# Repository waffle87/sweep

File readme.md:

# Sweep

A [Ferris Sweep](https://github.com/davidphilipbarr/Sweep) variant designed with an integrated RP2040 and some other added features.

## Comments & Modifications
This PCB has the exact same dimensions and mounting points (via SplitKB Tenting Puck mount) as original Sweep PCB, making it compatible with most existing cases. Due to the use of USB-C interconnects opposed to TRRS jacks, this PCB is **not** compatible with "high-profile" cases or cases that have a cutout for TRRS jacks. This PCB only supports soldered Choc V1 switches, as it is common to build this keyboard without a plate. Some other modifications include:
- Per-key RGB lighting and underglow
- Support for a 135x240 ST7789 LCD via an FPC connector/cable
- USB-C interconnects with full-duplex serial communication
- VBUS detection for setting handedness
- Current and voltage reading sensor
- RGB data level-shifted to 5v

## Ordering
The following instructions will be for [JLCPCB](https://jlcpcb.com), but should generally apply to most PCB manufacturers. If you would like a plate, the one [here](https://github.com/davidphilipbarr/Sweep/blob/main/Sweep%20v2.2/sweepv2_plate.pro) can probably be used, although I have not verified this.

1. Upload the Gerber files from [production/gerbers.zip](production/gerbers.zip)
2. Set the following parameters: (and change other things like PCB quantity and colour as desired)
- **Different Design**: 2
3. For PCB assembly, choose **Economic** PCBA type and **Top Side** for assembly side. If you would like the LEDs and related components to be installed by PCBA, choose **Standard** and **Both Sides**.
4. Upload the [BOM](production/bom.csv) and [CPL](production/positions.csv) files
5. Ensure the correct components have been selected, and all are in stock. An effort has been made to choose as few extended components as possible, but this is not possible for some.
- Footprints D1 & D2 are power indication LEDs. They can be left unpopulated if you'd rather not have an LED that is always lit. If you would like them installed while not being blinded, try to find an LED with a lower forward current and voltage (supply is 5v), perhaps something in the realm of 2v and 1-5mA.
- The current-smoothing capacitors (on the back side) for the RGB LEDs are not required for the LEDs to function.
- The FPC connector is only needed if you'd wish to install the ST7789 display(s).
6. Give a quick look at the component placement and make sure nothing looks wildly wrong. It is normal for some components to be shown oriented incorrectly or not quite where they belong. The PCB reviewers will usually correct this without issue.

### Additional components
For optional components to be installed by hand:
| Item | Quantity | Remarks |
|------|----------|---------|
| ST7789 135x240 Display ([Aliexpress](https://www.aliexpress.us/item/3256803585877182.html)) | 2 | Others with a matching pinout and 0.5mm pitch should work |
| Acrylic Cover ([cover.dxf](cover.dxf)) | 2 | Each uses 4x ~4mm M2 screws and 2x ~4mm M2 standofffs |

## Build Instructions
These steps assume you already have an assembled PCB and are installing switches, RGB LEDs, and/or displays. If you are hand-assembling the PCBs with all components, the [interactive BOM](https://html-preview.github.io/?url=https://github.com/waffle87/sweep/blob/master/ibom.html) will be helpful.

1. Ensure keyboard is functional by flashing firmware and testing by shorting switch footprint pins with metal tweezers. This should output keypresses on the computer.
2. Install RGB LEDs if desired. The chopped-off corner should align with the marked corner on PCB - this applies to both per-key and underglow LEDs. Please double check orientation, as an incorrectly oriented LED will result in keyboard not working. It is wise to test the LEDs as you install them (eg. install a couple, then plug in keyboard). The per-key LEDs will need to be installed and working before the underglow LEDs will work.
- If you choose to install the capacitors, do so at this step as well. They do not have a specific orientation.
3. Install displays if desired. Open FPC connector, insert display cable with contacts facing upward, close connector. The displays can be secured by some double sided tape, or carefully applying some hot glue.
4. Install switches, keycaps, case, and enjoy your keyboard!

## Firmware
QMK Firmware support for this keyboard can be found [here](https://git.pngu.org/qmk_me/tree/keyboards/sweep). Enter bootloader mode by holding BOOT button and tapping RESET button. If your PCBs are revision 0.1.0 (or have commit `2fa9763` labeled on them), you should use the code from [this commit](https://git.pngu.org/qmk_me/tree/keyboards/sweep?id=b0c6852154b3060b639e8d7d87d16d17bd4dfcc4) or prior.

## Changelog
### 0.2.0
- Remove Cirque trackpad support
- Remove nice!view and I2C OLED support
- Update to Kicad 9.0.2
- Add ST7789 LCD support
- Update acrylic cover and its mounting points
- Add voltage sensor support

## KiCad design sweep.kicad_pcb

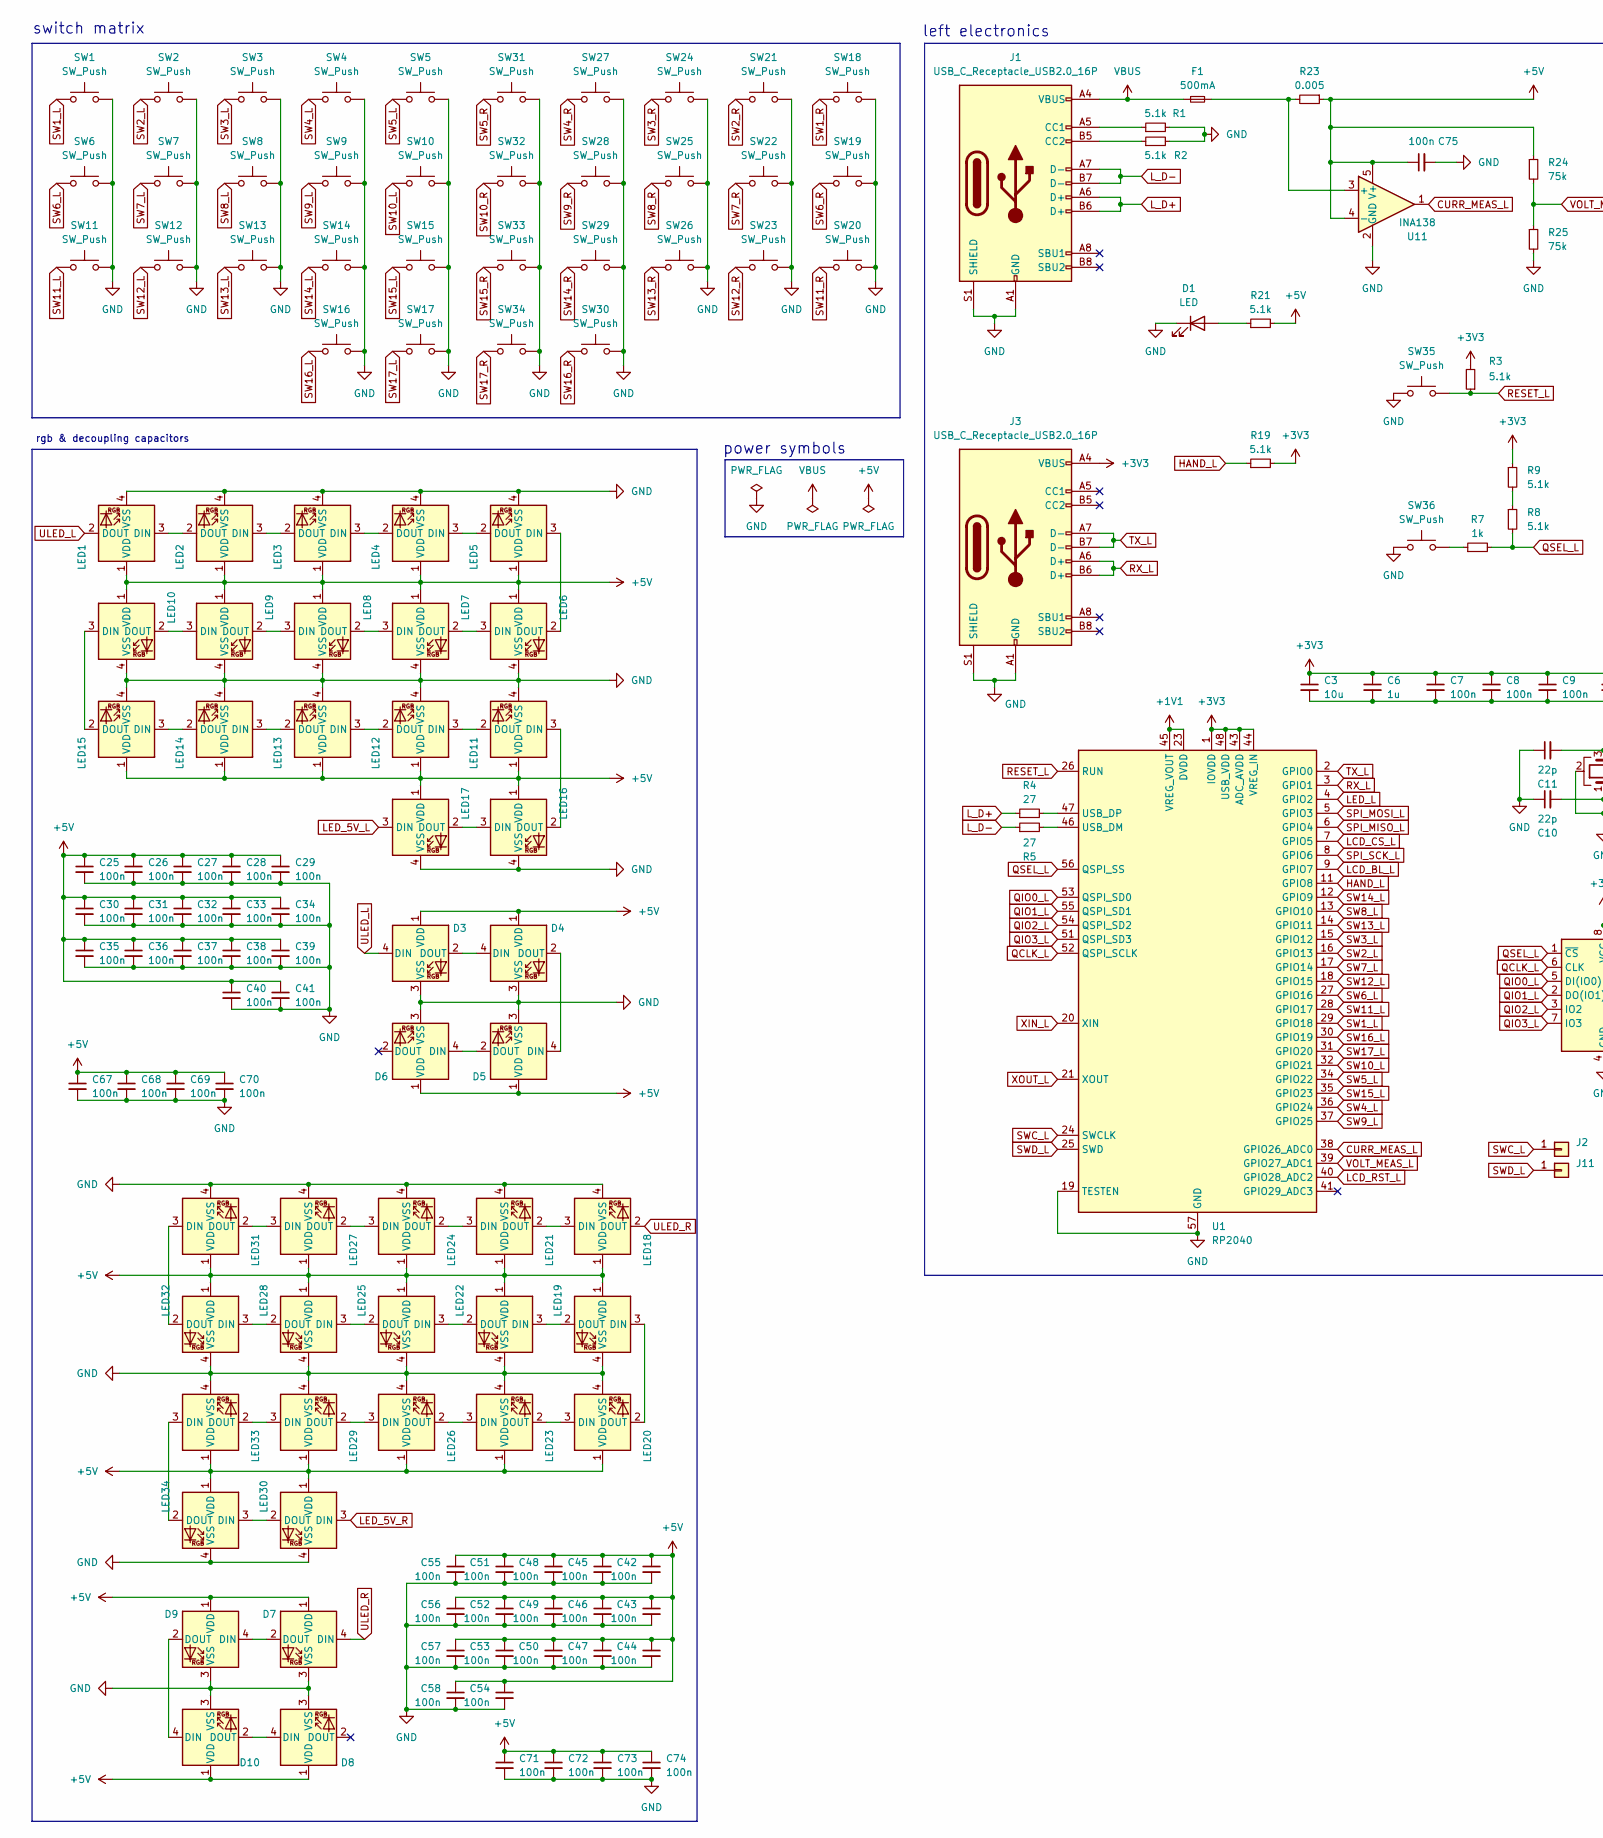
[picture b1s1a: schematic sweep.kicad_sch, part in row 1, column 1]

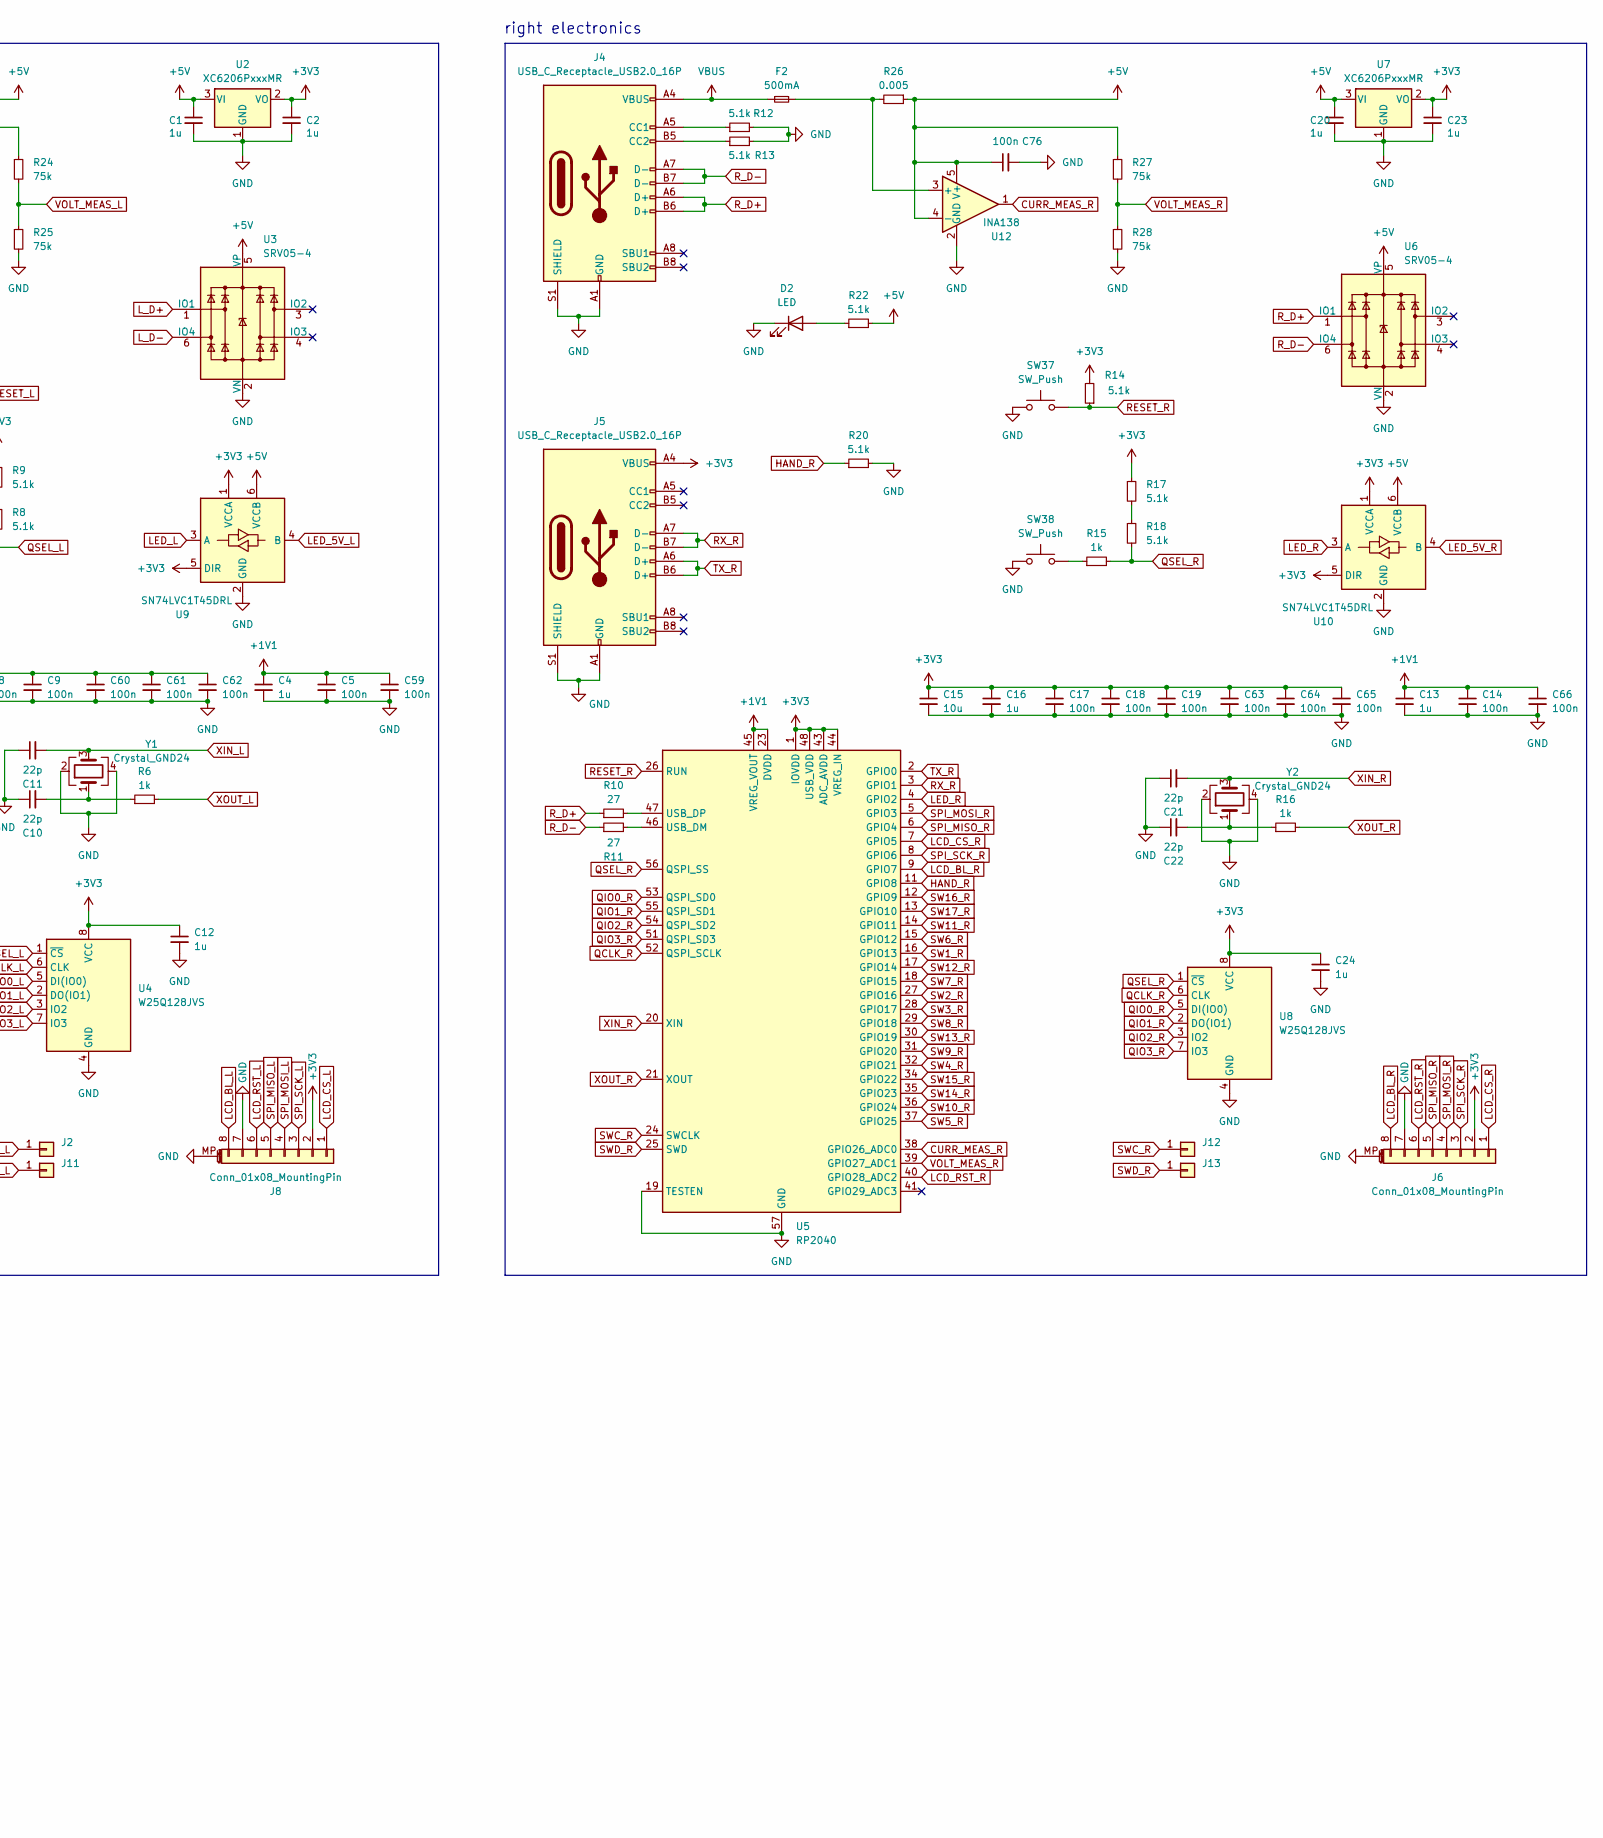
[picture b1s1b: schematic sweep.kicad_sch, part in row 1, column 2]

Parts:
C1, C2, C4, C6, C12, C13, C16, C20, C23, C24: 1u; C_0402_1005Metric
C3, C15: 10u; C_0603_1608Metric
C5, C7, C8, C9, C14, C17, C18, C19, C25, C26, C27, C28, C29, C30, C31, C32, C33, C34, C35, C36, C37, C38, C39, C40, C41, C42, C43, C44, C45, C46, C47, C48, C49, C50, C51, C52, C53, C54, C55, C56, C57, C58, C59, C60, C61, C62, C63, C64, C65, C66, C67, C68, C69, C70, C71, C72, C73, C74, C75, C76: 100n; C_0402_1005Metric
C10, C11, C21, C22: 22p; C_0402_1005Metric
D1, D2: LED; LED_0603_1608Metric
D3, D4, D5, D6, D7, D8, D9, D10: WS2812B; LED_WS2812B-Mini_PLCC4_3.5x3.5mm
F1, F2: 500mA; Fuse_1206_3216Metric
J1, J3, J4, J5: USB_C_Receptacle_USB2.0_16P; USB_C_Receptacle_HRO_TYPE-C-31-M-12
J2, J11, J12, J13: Conn_01x01; TestPoint_Pad_D1.0mm
J6, J8: Conn_01x08_MountingPin; TE_0-1734839-8_1x08-1MP_P0.5mm_Horizontal
LED1, LED2, LED3, LED4, LED5, LED6, LED7, LED8, LED9, LED10, LED11, LED12, LED13, LED14, LED15, LED16, LED17, LED18, LED19, LED20, LED21, LED22, LED23, LED24, LED25, LED26, LED27, LED28, LED29, LED30, LED31, LED32, LED33, LED34: choc_SK6812MINI-E; LED_choc_6028R
R1, R2, R3, R8, R9, R12, R13, R14, R17, R18, R19, R20, R21, R22: 5.1k; R_0402_1005Metric
R4, R5, R10, R11: 27; R_0402_1005Metric
R6, R7, R15, R16: 1k; R_0402_1005Metric
R23, R26: 0.005; R_1206_3216Metric
R24, R25, R27, R28: 75k; R_0402_1005Metric
SW1, SW2, SW3, SW4, SW5, SW6, SW7, SW8, SW9, SW10, SW11, SW12, SW13, SW14, SW15, SW16, SW17, SW18, SW19, SW20, SW21, SW22, SW23, SW24, SW25, SW26, SW27, SW28, SW29, SW30, SW31, SW32, SW33, SW34: SW_Push; SW_choc_v1_1u
SW35, SW36, SW37, SW38: SW_Push; SW_SPST_B3U-1000P
U1, U5: RP2040; QFN-56-1EP_7x7mm_P0.4mm_EP3.2x3.2mm
U2, U7: XC6206PxxxMR; SOT-23-3
U3, U6: SRV05-4; SOT-23-6-routable
U4, U8: W25Q128JVS; SOIC-8_5.23x5.23mm_P1.27mm
U9, U10: SN74LVC1T45DRL; SOT-563
U11, U12: INA138; SOT-23-5
Y1, Y2: Crystal_GND24; Crystal_SMD_3225-4Pin_3.2x2.5mm

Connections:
+1V1: C4.1, C5.1, C13.1, C14.1, C59.1, C66.1, U1.23 (DVDD), U1.45 (VREG_VOUT), U1.50 (DVDD), U5.23 (DVDD), U5.45 (VREG_VOUT), U5.50 (DVDD)
+3V3: C2.1, C3.1, C6.1, C7.1, C8.1, C9.1, C12.1, C15.1, C16.1, C17.1, C18.1, C19.1, C23.1, C24.1, C60.1, C61.1, C62.1, C63.1, C64.1, C65.1, J3.A4 (VBUS), J3.A9 (VBUS), J3.B4 (VBUS), J3.B9 (VBUS), J5.A4 (VBUS), J5.A9 (VBUS), J5.B4 (VBUS), J5.B9 (VBUS), J6.2, J8.2, R3.2, R9.1, R14.2, R17.1, R19.2, U1.1 (IOVDD), U1.10 (IOVDD), U1.22 (IOVDD), U1.33 (IOVDD), U1.42 (IOVDD), U1.43 (ADC_AVDD), U1.44 (VREG_IN), U1.48 (USB_VDD), U1.49 (IOVDD), U2.2 (VO), U4.8 (VCC), U5.1 (IOVDD), U5.10 (IOVDD), U5.22 (IOVDD), U5.33 (IOVDD), U5.42 (IOVDD), U5.43 (ADC_AVDD), U5.44 (VREG_IN), U5.48 (USB_VDD), U5.49 (IOVDD), U7.2 (VO), U8.8 (VCC), U9.1 (VCCA), U9.5 (DIR), U10.1 (VCCA), U10.5 (DIR)
+5V: C1.1, C20.1, C25.1, C26.1, C27.1, C28.1, C29.1, C30.1, C31.1, C32.1, C33.1, C34.1, C35.1, C36.1, C37.1, C38.1, C39.1, C40.1, C41.1, C42.1, C43.1, C44.1, C45.1, C46.1, C47.1, C48.1, C49.1, C50.1, C51.1, C52.1, C53.1, C54.1, C55.1, C56.1, C57.1, C58.1, C67.1, C68.1, C69.1, C70.1, C71.1, C72.1, C73.1, C74.1, C75.1, C76.1, D3.1 (VDD), D4.1 (VDD), D5.1 (VDD), D6.1 (VDD), D7.1 (VDD), D8.1 (VDD), D9.1 (VDD), D10.1 (VDD), LED1.1 (VDD), LED2.1 (VDD), LED3.1 (VDD), LED4.1 (VDD), LED5.1 (VDD), LED6.1 (VDD), LED7.1 (VDD), LED8.1 (VDD), LED9.1 (VDD), LED10.1 (VDD), LED11.1 (VDD), LED12.1 (VDD), LED13.1 (VDD), LED14.1 (VDD), LED15.1 (VDD), LED16.1 (VDD), LED17.1 (VDD), LED18.1 (VDD), LED19.1 (VDD), LED20.1 (VDD), LED21.1 (VDD), LED22.1 (VDD), LED23.1 (VDD), LED24.1 (VDD), LED25.1 (VDD), LED26.1 (VDD), LED27.1 (VDD), LED28.1 (VDD), LED29.1 (VDD), LED30.1 (VDD), LED31.1 (VDD), LED32.1 (VDD), LED33.1 (VDD), LED34.1 (VDD), R21.2, R22.2, R23.1, R24.1, R26.1, R27.1, U2.3 (VI), U3.5 (VP), U6.5 (VP), U7.3 (VI), U9.6 (VCCB), U10.6 (VCCB), U11.4 (-), U11.5 (V+), U12.4 (-), U12.5 (V+)
CURR_MEAS_L: U1.38 (GPIO26_ADC0), U11.1
CURR_MEAS_R: U5.38 (GPIO26_ADC0), U12.1
GND: C1.2, C2.2, C3.2, C4.2, C5.2, C6.2, C7.2, C8.2, C9.2, C10.1, C11.1, C12.2, C13.2, C14.2, C15.2, C16.2, C17.2, C18.2, C19.2, C20.2, C21.1, C22.1, C23.2, C24.2, C25.2, C26.2, C27.2, C28.2, C29.2, C30.2, C31.2, C32.2, C33.2, C34.2, C35.2, C36.2, C37.2, C38.2, C39.2, C40.2, C41.2, C42.2, C43.2, C44.2, C45.2, C46.2, C47.2, C48.2, C49.2, C50.2, C51.2, C52.2, C53.2, C54.2, C55.2, C56.2, C57.2, C58.2, C59.2, C60.2, C61.2, C62.2, C63.2, C64.2, C65.2, C66.2, C67.2, C68.2, C69.2, C70.2, C71.2, C72.2, C73.2, C74.2, C75.2, C76.2, D1.1 (K), D2.1 (K), D3.3 (VSS), D4.3 (VSS), D5.3 (VSS), D6.3 (VSS), D7.3 (VSS), D8.3 (VSS), D9.3 (VSS), D10.3 (VSS), J1.A1 (GND), J1.A12 (GND), J1.B1 (GND), J1.B12 (GND), J1.S1 (SHIELD), J3.A1 (GND), J3.A12 (GND), J3.B1 (GND), J3.B12 (GND), J3.S1 (SHIELD), J4.A1 (GND), J4.A12 (GND), J4.B1 (GND), J4.B12 (GND), J4.S1 (SHIELD), J5.A1 (GND), J5.A12 (GND), J5.B1 (GND), J5.B12 (GND), J5.S1 (SHIELD), J6.7, J6.MP (MountPin), J8.7, J8.MP (MountPin), LED1.4 (VSS), LED2.4 (VSS), LED3.4 (VSS), LED4.4 (VSS), LED5.4 (VSS), LED6.4 (VSS), LED7.4 (VSS), LED8.4 (VSS), LED9.4 (VSS), LED10.4 (VSS), LED11.4 (VSS), LED12.4 (VSS), LED13.4 (VSS), LED14.4 (VSS), LED15.4 (VSS), LED16.4 (VSS), LED17.4 (VSS), LED18.4 (VSS), LED19.4 (VSS), LED20.4 (VSS), LED21.4 (VSS), LED22.4 (VSS), LED23.4 (VSS), LED24.4 (VSS), LED25.4 (VSS), LED26.4 (VSS), LED27.4 (VSS), LED28.4 (VSS), LED29.4 (VSS), LED30.4 (VSS), LED31.4 (VSS), LED32.4 (VSS), LED33.4 (VSS), LED34.4 (VSS), R1.2, R2.2, R12.2, R13.2, R20.2, R25.2, R28.2, SW1.2, SW2.2, SW3.2, SW4.2, SW5.2, SW6.2, SW7.2, SW8.2, SW9.2, SW10.2, SW11.2, SW12.2, SW13.2, SW14.2, SW15.2, SW16.2, SW17.2, SW18.1, SW19.1, SW20.1, SW21.1, SW22.1, SW23.1, SW24.1, SW25.1, SW26.1, SW27.1, SW28.1, SW29.1, SW30.1, SW31.1, SW32.1, SW33.1, SW34.1, SW35.1, SW36.1, SW37.1, SW38.1, U1.19 (TESTEN), U1.57 (GND), U2.1 (GND), U3.2 (VN), U4.4 (GND), U5.19 (TESTEN), U5.57 (GND), U6.2 (VN), U7.1 (GND), U8.4 (GND), U9.2 (GND), U10.2 (GND), U11.2 (GND), U12.2 (GND), Y1.2, Y1.4, Y2.2, Y2.4
HAND_L: R19.1, U1.11 (GPIO8)
HAND_R: R20.1, U5.11 (GPIO8)
LCD_BL_L: J8.8, U1.9 (GPIO7)
LCD_BL_R: J6.8, U5.9 (GPIO7)
LCD_CS_L: J8.1, U1.7 (GPIO5)
LCD_CS_R: J6.1, U5.7 (GPIO5)
LCD_RST_L: J8.6, U1.40 (GPIO28_ADC2)
LCD_RST_R: J6.6, U5.40 (GPIO28_ADC2)
LED_5V_L: LED17.3 (DIN), U9.4 (B)
LED_5V_R: LED30.3 (DIN), U10.4 (B)
LED_L: U1.4 (GPIO2), U9.3 (A)
LED_R: U5.4 (GPIO2), U10.3 (A)
L_D+: J1.A6 (D+), J1.B6 (D+), R4.1, U3.1 (IO1)
L_D-: J1.A7 (D-), J1.B7 (D-), R5.1, U3.6 (IO4)
unnamed: C10.2, R6.1, Y1.1
unnamed: C22.2, R16.1, Y2.1
unnamed: D1.2 (A), R21.1
unnamed: D2.2 (A), R22.1
unnamed: D3.2 (DOUT), D4.4 (DIN)
unnamed: D4.2 (DOUT), D5.4 (DIN)
unnamed: D5.2 (DOUT), D6.4 (DIN)
unnamed: D7.2 (DOUT), D9.4 (DIN)
unnamed: D9.2 (DOUT), D10.4 (DIN)
unnamed: D8.4 (DIN), D10.2 (DOUT)
unnamed: J1.A5 (CC1), R1.1
unnamed: J1.B5 (CC2), R2.1
unnamed: J4.A5 (CC1), R12.1
unnamed: J4.B5 (CC2), R13.1
unnamed: LED1.3 (DIN), LED2.2 (DOUT)
unnamed: LED2.3 (DIN), LED3.2 (DOUT)
unnamed: LED3.3 (DIN), LED4.2 (DOUT)
unnamed: LED4.3 (DIN), LED5.2 (DOUT)
unnamed: LED5.3 (DIN), LED6.2 (DOUT)
unnamed: LED6.3 (DIN), LED7.2 (DOUT)
unnamed: LED7.3 (DIN), LED8.2 (DOUT)
unnamed: LED8.3 (DIN), LED9.2 (DOUT)
unnamed: LED10.3 (DIN), LED15.2 (DOUT)
unnamed: LED9.3 (DIN), LED10.2 (DOUT)
unnamed: LED11.3 (DIN), LED16.2 (DOUT)
unnamed: LED11.2 (DOUT), LED12.3 (DIN)
unnamed: LED12.2 (DOUT), LED13.3 (DIN)
unnamed: LED13.2 (DOUT), LED14.3 (DIN)
unnamed: LED14.2 (DOUT), LED15.3 (DIN)
unnamed: LED16.3 (DIN), LED17.2 (DOUT)
unnamed: LED18.3 (DIN), LED21.2 (DOUT)
unnamed: LED19.3 (DIN), LED20.2 (DOUT)
unnamed: LED19.2 (DOUT), LED22.3 (DIN)
unnamed: LED20.3 (DIN), LED23.2 (DOUT)
unnamed: LED21.3 (DIN), LED24.2 (DOUT)
unnamed: LED22.2 (DOUT), LED25.3 (DIN)
unnamed: LED23.3 (DIN), LED26.2 (DOUT)
unnamed: LED24.3 (DIN), LED27.2 (DOUT)
unnamed: LED25.2 (DOUT), LED28.3 (DIN)
unnamed: LED26.3 (DIN), LED29.2 (DOUT)
unnamed: LED27.3 (DIN), LED31.2 (DOUT)
unnamed: LED28.2 (DOUT), LED32.3 (DIN)
unnamed: LED29.3 (DIN), LED33.2 (DOUT)
unnamed: LED30.2 (DOUT), LED34.3 (DIN)
unnamed: LED31.3 (DIN), LED32.2 (DOUT)
unnamed: LED33.3 (DIN), LED34.2 (DOUT)
unnamed: R7.1, SW36.2
unnamed: R8.1, R9.2
unnamed: R15.1, SW38.2
unnamed: R17.2, R18.1
unnamed: R5.2, U1.46 (USB_DM)
unnamed: R4.2, U1.47 (USB_DP)
unnamed: R11.2, U5.46 (USB_DM)
unnamed: R10.2, U5.47 (USB_DP)
unnamed: F1.2, R23.2, U11.3 (+)
unnamed: F2.2, R26.2, U12.3 (+)
QCLK_L: U1.52 (QSPI_SCLK), U4.6 (CLK)
QCLK_R: U5.52 (QSPI_SCLK), U8.6 (CLK)
QIO0_L: U1.53 (QSPI_SD0), U4.5 (DI(IO0))
QIO0_R: U5.53 (QSPI_SD0), U8.5 (DI(IO0))
QIO1_L: U1.55 (QSPI_SD1), U4.2 (DO(IO1))
QIO1_R: U5.55 (QSPI_SD1), U8.2 (DO(IO1))
QIO2_L: U1.54 (QSPI_SD2), U4.3 (IO2)
QIO2_R: U5.54 (QSPI_SD2), U8.3 (IO2)
QIO3_L: U1.51 (QSPI_SD3), U4.7 (IO3)
QIO3_R: U5.51 (QSPI_SD3), U8.7 (IO3)
QSEL_L: R7.2, R8.2, U1.56 (QSPI_SS), U4.1 (~CS)
QSEL_R: R15.2, R18.2, U5.56 (QSPI_SS), U8.1 (~CS)
RESET_L: R3.1, SW35.2, U1.26 (RUN)
RESET_R: R14.1, SW37.2, U5.26 (RUN)
RX_L: J3.A6 (D+), J3.B6 (D+), U1.3 (GPIO1)
RX_R: J5.A7 (D-), J5.B7 (D-), U5.3 (GPIO1)
R_D+: J4.A6 (D+), J4.B6 (D+), R10.1, U6.1 (IO1)
R_D-: J4.A7 (D-), J4.B7 (D-), R11.1, U6.6 (IO4)
SPI_MISO_L: J8.5, U1.6 (GPIO4)
SPI_MISO_R: J6.5, U5.6 (GPIO4)
SPI_MOSI_L: J8.4, U1.5 (GPIO3)
SPI_MOSI_R: J6.4, U5.5 (GPIO3)
SPI_SCK_L: J8.3, U1.8 (GPIO6)
SPI_SCK_R: J6.3, U5.8 (GPIO6)
SW1_L: SW1.1, U1.29 (GPIO18)
SW1_R: SW18.2, U5.16 (GPIO13)
SW2_L: SW2.1, U1.16 (GPIO13)
SW2_R: SW21.2, U5.27 (GPIO16)
SW3_L: SW3.1, U1.15 (GPIO12)
SW3_R: SW24.2, U5.28 (GPIO17)
SW4_L: SW4.1, U1.36 (GPIO24)
SW4_R: SW27.2, U5.32 (GPIO21)
SW5_L: SW5.1, U1.34 (GPIO22)
SW5_R: SW31.2, U5.37 (GPIO25)
SW6_L: SW6.1, U1.27 (GPIO16)
SW6_R: SW19.2, U5.15 (GPIO12)
SW7_L: SW7.1, U1.17 (GPIO14)
SW7_R: SW22.2, U5.18 (GPIO15)
SW8_L: SW8.1, U1.13 (GPIO10)
SW8_R: SW25.2, U5.29 (GPIO18)
SW9_L: SW9.1, U1.37 (GPIO25)
SW9_R: SW28.2, U5.31 (GPIO20)
SW10_L: SW10.1, U1.32 (GPIO21)
SW10_R: SW32.2, U5.36 (GPIO24)
SW11_L: SW11.1, U1.28 (GPIO17)
SW11_R: SW20.2, U5.14 (GPIO11)
SW12_L: SW12.1, U1.18 (GPIO15)
SW12_R: SW23.2, U5.17 (GPIO14)
SW13_L: SW13.1, U1.14 (GPIO11)
SW13_R: SW26.2, U5.30 (GPIO19)
SW14_L: SW14.1, U1.12 (GPIO9)
SW14_R: SW29.2, U5.35 (GPIO23)
SW15_L: SW15.1, U1.35 (GPIO23)
SW15_R: SW33.2, U5.34 (GPIO22)
SW16_L: SW16.1, U1.30 (GPIO19)
SW16_R: SW30.2, U5.12 (GPIO9)
SW17_L: SW17.1, U1.31 (GPIO20)
SW17_R: SW34.2, U5.13 (GPIO10)
SWC_L: J2.1, U1.24 (SWCLK)
SWC_R: J12.1, U5.24 (SWCLK)
SWD_L: J11.1, U1.25 (SWD)
SWD_R: J13.1, U5.25 (SWD)
TX_L: J3.A7 (D-), J3.B7 (D-), U1.2 (GPIO0)
TX_R: J5.A6 (D+), J5.B6 (D+), U5.2 (GPIO0)
ULED_L: D3.4 (DIN), LED1.2 (DOUT)
ULED_R: D7.4 (DIN), LED18.2 (DOUT)
VBUS: F1.1, F2.1, J1.A4 (VBUS), J1.A9 (VBUS), J1.B4 (VBUS), J1.B9 (VBUS), J4.A4 (VBUS), J4.A9 (VBUS), J4.B4 (VBUS), J4.B9 (VBUS)
VOLT_MEAS_L: R24.2, R25.1, U1.39 (GPIO27_ADC1)
VOLT_MEAS_R: R27.2, R28.1, U5.39 (GPIO27_ADC1)
XIN_L: C11.2, U1.20 (XIN), Y1.3
XIN_R: C21.2, U5.20 (XIN), Y2.3
XOUT_L: R6.2, U1.21 (XOUT)
XOUT_R: R16.2, U5.21 (XOUT)

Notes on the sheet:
switch matrix
rgb & decoupling capacitors
left electronics
power symbols
right electronics

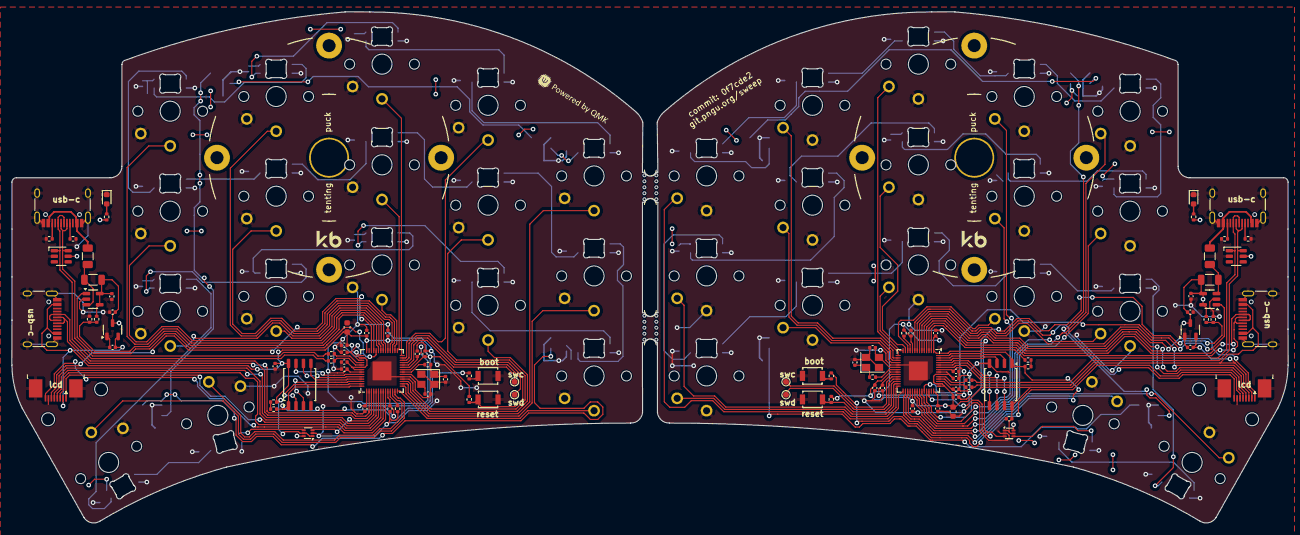
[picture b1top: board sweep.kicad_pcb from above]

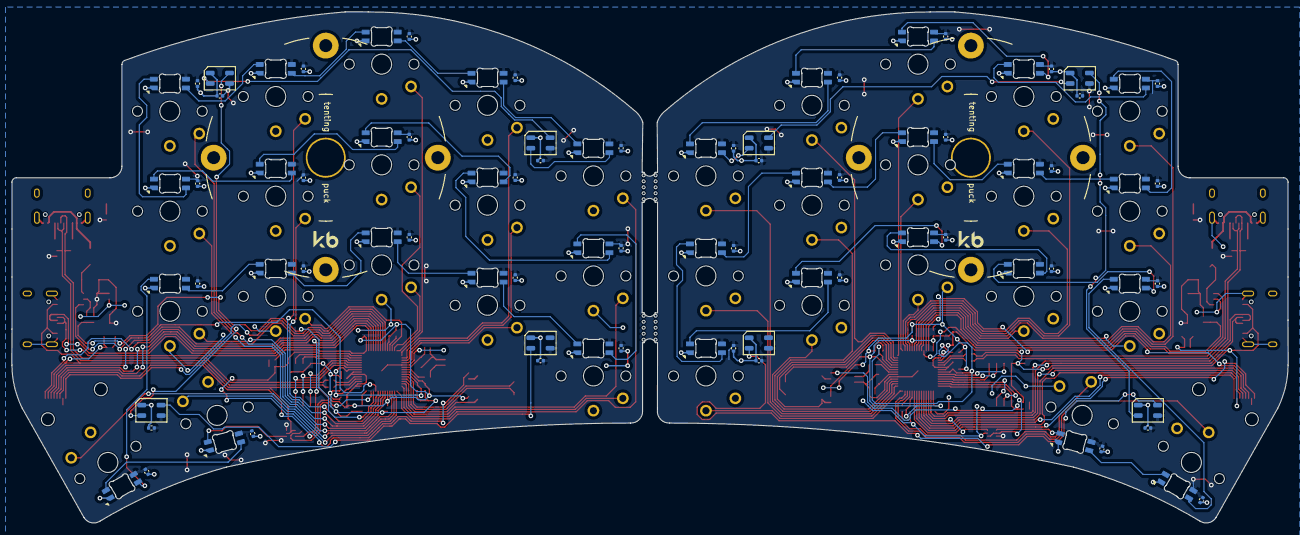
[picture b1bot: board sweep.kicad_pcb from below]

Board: 2 copper layers, 216.9 x 86.9 mm, 214 parts (84 on the bottom side), 149 nets.

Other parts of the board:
mouse-bite-2mm-slot, mouse-bite-2mm-slot#2: VAL**; mouse-bite-5mm-slot-with-space-for-track

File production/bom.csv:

Designator,Footprint,Quantity,Value,LCSC Part #
"C1, C12, C13, C16, C2, C20, C23, C24, C4, C6",0402,10,1u,C52923
"C10, C11, C21, C22",0402,4,22p,C1555
"C14, C17, C18, C19, C25, C26, C27, C28, C29, C30, C31, C32, C33, C34, C35, C36, C37, C38, C39, C40, C41, C42, C43, C44, C45, C46, C47, C48, C49, C5, C50, C51, C52, C53, C54, C55, C56, C57, C58, C59, C60, C61, C62, C63, C64, C65, C66, C67, C68, C69, C7, C70, C71, C72, C73, C74, C75, C76, C8, C9",0402,60,100n,C1525
"C15, C3",0603,2,10u,C19702
"D1, D2",0603,2,LED,C2286
"D10, D3, D4, D5, D6, D7, D8, D9",LED_WS2812B-Mini_PLCC4_3.5x3.5mm,8,WS2812B,C527089
"F1, F2",1206,2,500mA,C70070
"J1, J3, J4, J5",USB_C_Receptacle_HRO_TYPE-C-31-M-12,4,USB_C_Receptacle_USB2.0_16P,C165948
"J6, J8",TE_0-1734839-8_1x08-1MP_P0.5mm_Horizontal,2,Conn_01x08_MountingPin,C5373445
"LED1, LED10, LED11, LED12, LED13, LED14, LED15, LED16, LED17, LED18, LED19, LED2, LED20, LED21, LED22, LED23, LED24, LED25, LED26, LED27, LED28, LED29, LED3, LED30, LED31, LED32, LED33, LED34, LED4, LED5, LED6, LED7, LED8, LED9",LED_choc_6028R,34,choc_SK6812MINI-E,C5149201
"R1, R12, R13, R14, R17, R18, R19, R2, R20, R21, R22, R3, R8, R9",0402,14,5.1k,C25905
"R10, R11, R4, R5",0402,4,27,C138021
"R15, R16, R6, R7",0402,4,1k,C11702
"R23, R26",1206,2,0.005,C912768
"R24, R25, R27, R28",0402,4,75k,C137935
"SW35, SW36, SW37, SW38",SW_SPST_B3U-1000P,4,SW_Push,C231329
"U1, U5",QFN-56-1EP_7x7mm_P0.4mm_EP3.2x3.2mm,2,RP2040,C2040
"U10, U9",SOT-563,2,SN74LVC1T45DRL,C352970
"U11, U12",SOT-23-5,2,INA138,C47914
"U2, U7",SOT-23-3,2,XC6206PxxxMR,C5446
"U3, U6",SOT-23-6-routable,2,SRV05-4,C558418
"U4, U8",SOIC-8_5.23x5.23mm_P1.27mm,2,W25Q128JVS,C97521
"Y1, Y2",Crystal_SMD_3225-4Pin_3.2x2.5mm,2,Crystal_GND24,C9002

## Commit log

2024-08-10 Adds integrated RP2040 PCBs, production files, and initial documentation
2024-08-10 Add silkscreen graphics
2024-08-17 Fix some part numbers, add more notes, add images
2024-08-20 Add 2D cover file & update readme
2024-09-08 Touch up readme & add images
2025-06-04 Adds updated PCBs (see changelog) and production files
2025-06-04 Update silkscreen graphics, interactive bom, and svg's
2025-06-06 Update acrylic cover, correct some part numbers, and readme updates
2025-06-18 Fix FPC connector pinout, minor readme syntax updates
2025-06-18 Update silkscreen graphics, BOM, and gerbers

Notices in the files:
sweep.kicad_pcb:
Solderpad Hardware License v2.1
